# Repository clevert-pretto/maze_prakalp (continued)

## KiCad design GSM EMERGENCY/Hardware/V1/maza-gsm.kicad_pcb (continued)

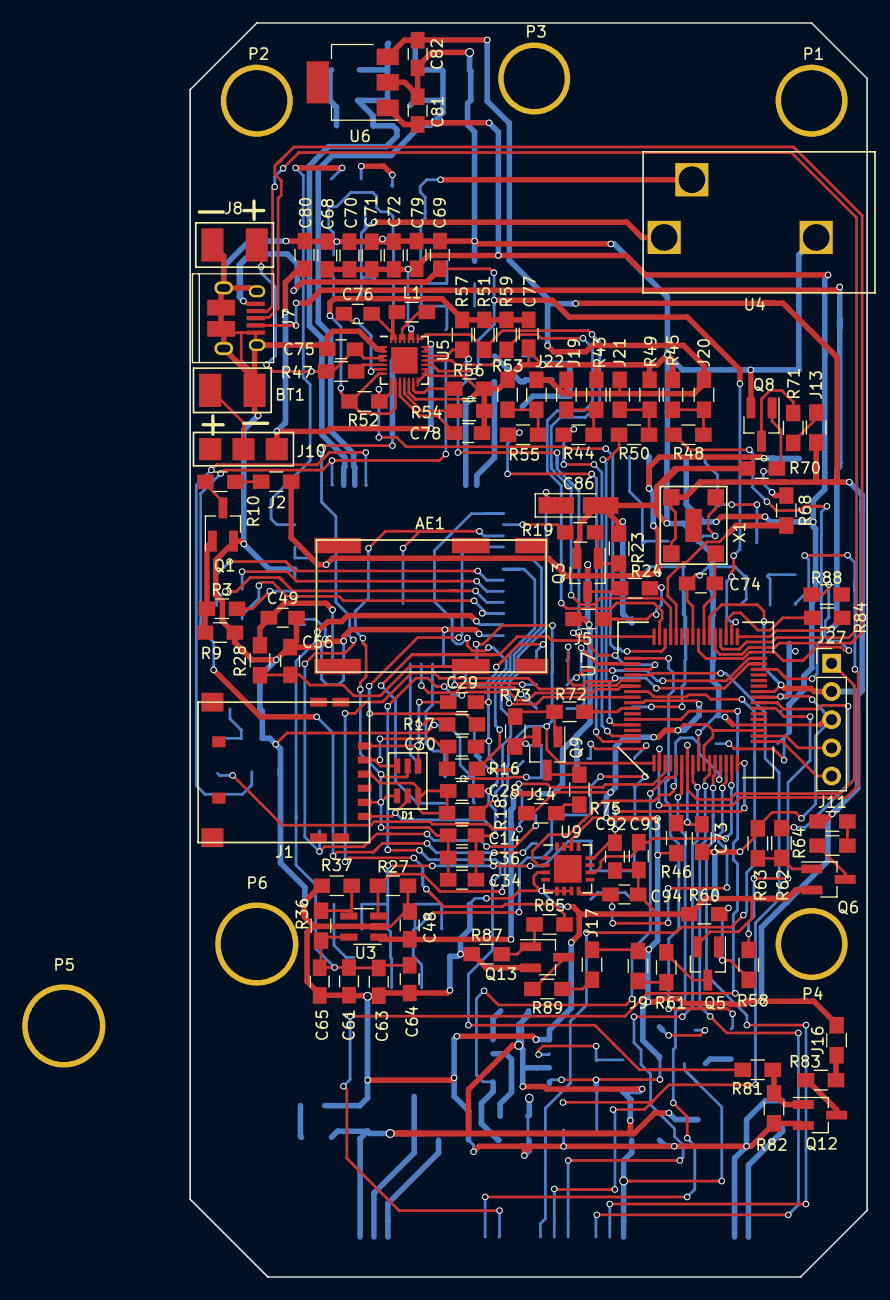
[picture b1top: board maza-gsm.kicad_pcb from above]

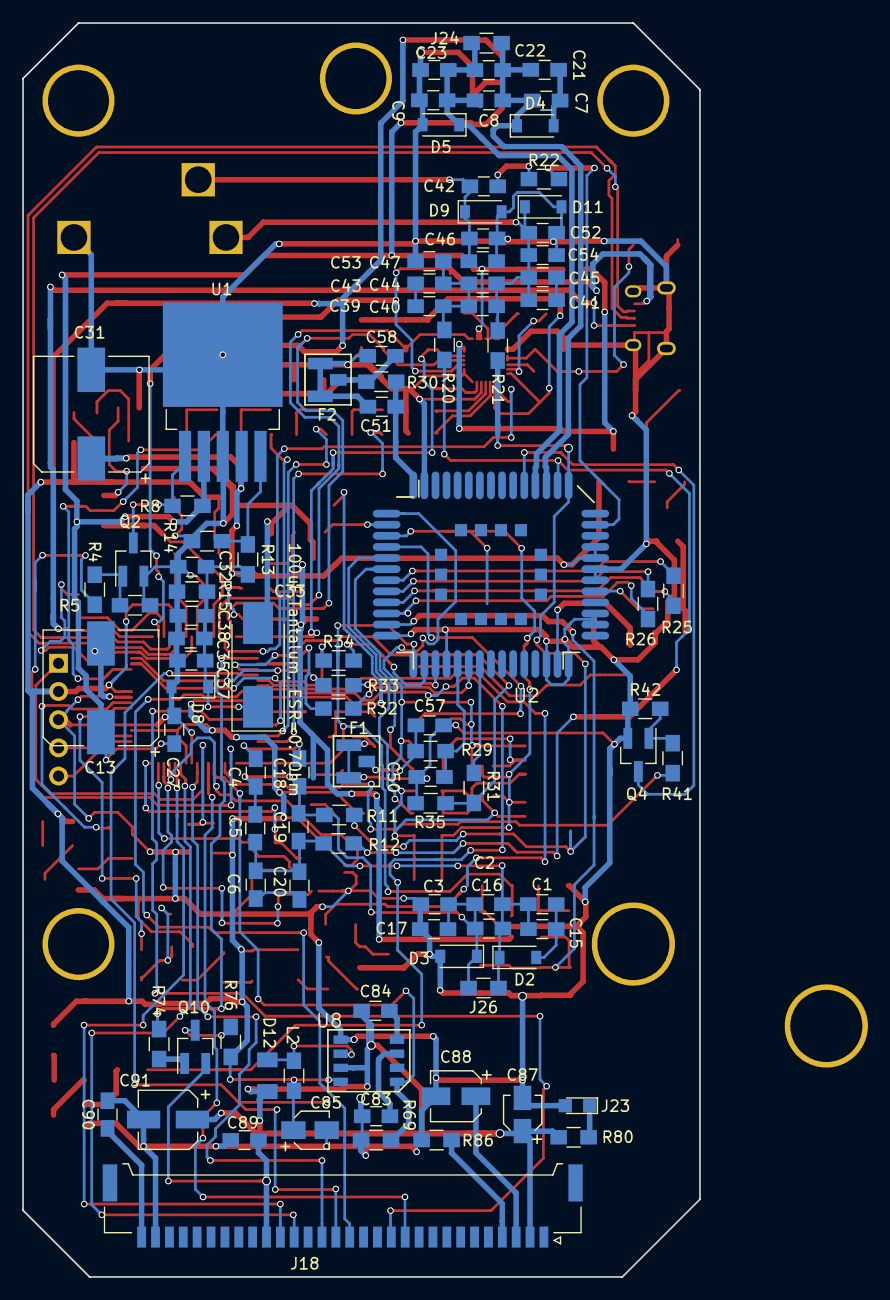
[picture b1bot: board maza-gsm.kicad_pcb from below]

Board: 2 copper layers, 61.0 x 113.0 mm, 221 parts (98 on the bottom side), 147 nets.

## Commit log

2017-04-01 Schematics updated
2017-04-08 Added the pcb file and schematics for GSM section
2017-04-10 Added sch for OLED,OSC,PB
2017-04-15 sch added TVS doide in SIM interface
2017-04-22 Completed till schematics
2017-04-27 Added the Accelerometer in sch.
2017-05-03 Loaded netlist to pcbnew and sorted components, added pcb keepout
2017-05-13 PCB completed
2017-05-16 Firmware baseline v1
